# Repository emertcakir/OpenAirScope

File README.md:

EMC
------
# OpenAirScope 🌍💨

**OpenAirScope** is an open-source hardware and software project designed for advanced environmental monitoring and air quality measurement. It is based on the STM32H743 and ESP32-C3, supports LoRaWAN, and is equipped with a wide range of up-to-date sensors and display options.

### PCB 3D

## Features

* **High-Performance MCU**:

  * STM32H743 (ARM Cortex-M7, 400 MHz)
  * Capable of running advanced algorithms and real-time data processing
  * Multiple communication interfaces (I²C, SPI, UART, CAN, USB, RS485)

* **Wireless Communication**:

  * **ESP32-C3-WROOM-02** → Wi-Fi + Bluetooth LE
  * **RAK3172 (LoRaWAN)** → Low-power, long-range wireless communication
  * External **SMA antenna connector** (for LoRa)

* **Sensor Support (Optional/Modular)**:

  * **SGP41-D-R4** → Gas sensor (VOC and NOx measurement)
  * **SCD40-D-R2** → CO₂, temperature, and humidity sensor
  * **SPS30** → Particulate matter sensor (PM1.0, PM2.5, PM4, PM10)
  * **LTR-303ALS-01 (Optional)** → Ambient light sensor
  * **SPH0645LM4H-B (2 units)** → Digital MEMS microphone (ambient noise, sound level, acoustic analysis)
  * Expandable design: additional sensors such as pressure or UV can be integrated

* **Display**:

  * **1.5-inch RGB OLED Display Module**
  * 65K RGB colors, 128×128 resolution
  * SPI interface for fast graphics and real-time data visualization

* **Power Management**:

  * **Li-Ion battery support**
  * USB-powered with **simultaneous battery charging**
  * Suitable for both portable and stationary applications

* **Flexible Communication**:

  * USB-C interface
  * RS485 (for industrial environments)
  * CAN-Bus support
  * IoT integration via Wi-Fi and LoRaWAN

* **Modular Design**:

  * Optional sensor add/remove capability
  * External SMA antenna for long-range connectivity
  * Developer-friendly accessible pinout

* **Software**:

  * STM32CubeIDE / PlatformIO support
  * Open-source drivers and example libraries
  * Example algorithms for air quality and environmental data evaluation
  * OLED display example code for real-time visualization of sensor data

## Use Cases

* Smart city solutions
* Industrial environment monitoring
* Indoor/outdoor air quality tracking
* Noise pollution and sound analysis
* Portable IoT devices with OLED display
* Long-range LoRaWAN field applications
* Research and education projects

## Contributing

This project is open source. Contributions are welcome for new sensor support, software development, or documentation improvements. You can submit pull requests or open issues.

## License

Released under the MIT License.

CRITICAL WARNING: This PCB design is currently an experimental, unverified prototype (AS-IS). I have not yet manufactured or functionally tested this version. Proceeding with production carries a high risk of failure and is undertaken solely at your own risk.
---

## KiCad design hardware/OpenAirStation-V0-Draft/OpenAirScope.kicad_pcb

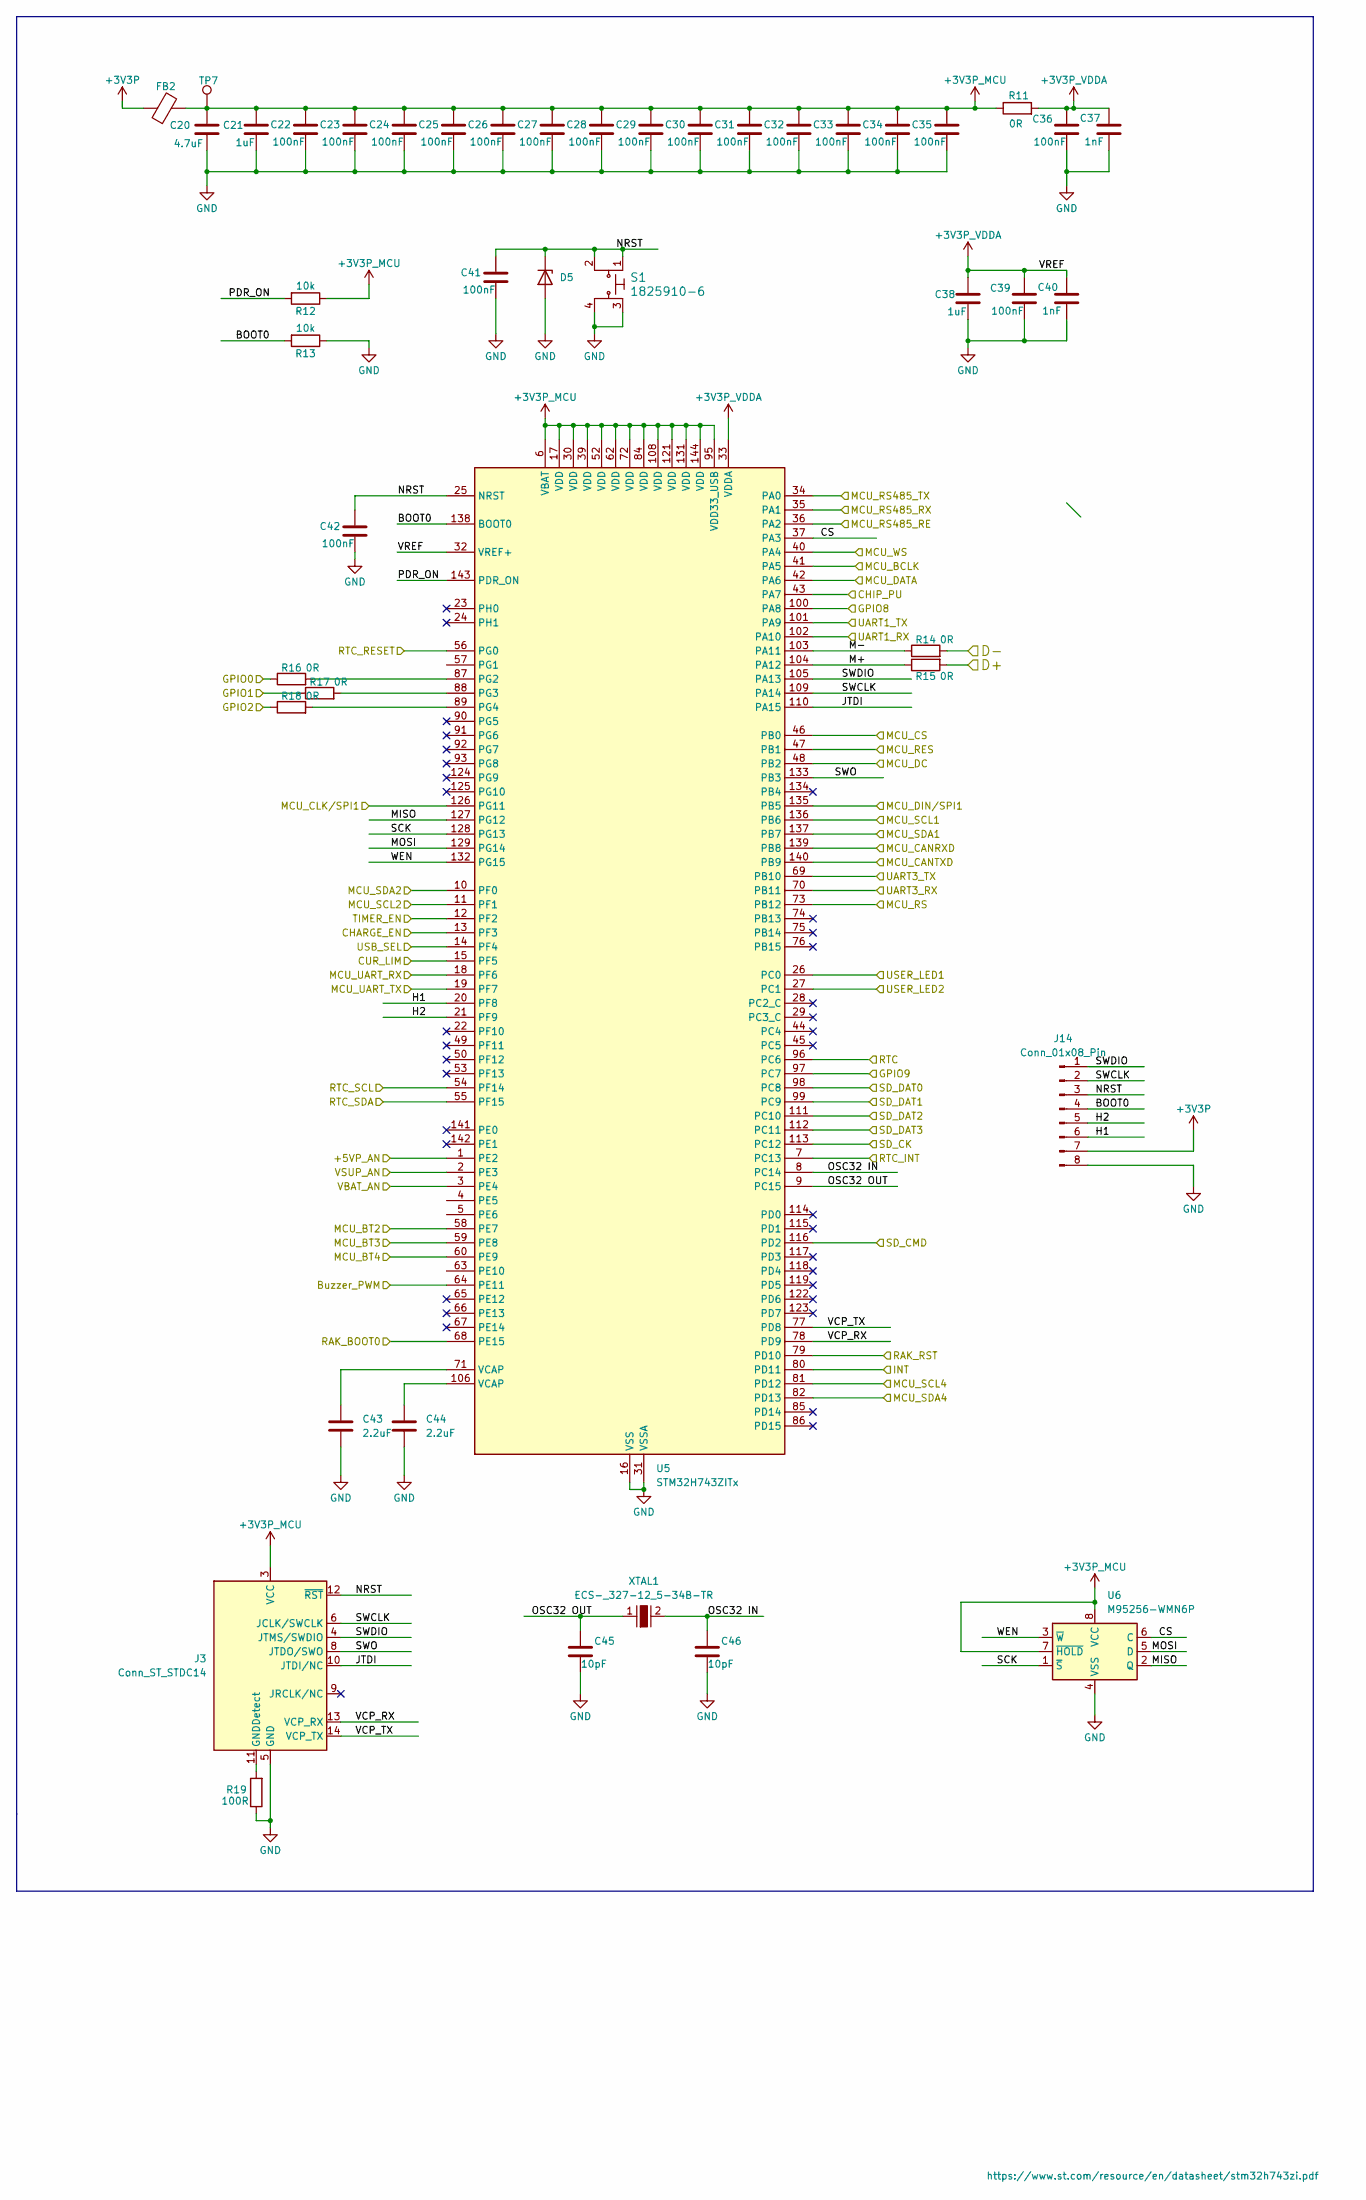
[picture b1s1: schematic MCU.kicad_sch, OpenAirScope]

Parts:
C20: 4.7uF; C_0805_2012Metric
C21, C38: 1uF; C_1206_3216Metric
C22, C23, C24, C25, C26, C27, C28, C29, C30, C31, C32, C33, C34, C35, C36, C39, C41, C42: 100nF; C_0603_1608Metric
C37, C40: 1nF; C_0603_1608Metric
C43, C44: 2.2uF; C_1206_3216Metric
C45, C46: 10pF; C_0603_1608Metric
D5: PTVS5V0Z1USKYL; Nexperia_DSN1608-2_1.6x0.8mm
FB2: FerriteBead; L_0603_1608Metric
J3: Conn_ST_STDC14; PinHeader_2x07_P1.27mm_Vertical
J14: Conn_01x08_Pin; PinHeader_1x08_P2.54mm_Vertical
R11, R14, R15, R16, R17, R18: 0R; R_0603_1608Metric
R12, R13: 10k; R_0603_1608Metric
R19: 100R; R_0603_1608Metric
S1: 1825910-6; Switch_Tactile_THT_6x6mm; MPN 1825910-6; Digi-Key_PN 450-1650-ND
TP7: TestPoint; TestPoint_Pad_D1.0mm
U5: STM32H743ZITx; LQFP-144_20x20mm_P0.5mm
U6: M95256-WMN6P; SOIC-8_3.9x4.9mm_P1.27mm
XTAL1: ECS-_327-12_5-34B-TR; SMD-2_3.2x1.5mm; MPN ECS-.327-12.5-34B-TR; Digi-Key_PN XC1617CT-ND

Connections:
+3V3P: FB2.1, J14.7; also elsewhere on the board
+3V3P_MCU: C20.1, C21.1, C22.2, C23.2, C24.2, C25.2, C26.2, C27.2, C28.2, C29.2, C30.2, C31.2, C32.2, C33.2, C34.2, C35.2, FB2.2, J3.3 (VCC), R11.1, R12.1, TP7.1, U5.6 (VBAT), U5.17 (VDD), U5.30 (VDD), U5.39 (VDD), U5.52 (VDD), U5.62 (VDD), U5.72 (VDD), U5.84 (VDD), U5.95 (VDD33_USB), U5.108 (VDD), U5.121 (VDD), U5.131 (VDD), U5.144 (VDD), U6.7 (~HOLD), U6.8 (VCC)
+3V3P_VDDA: C36.2, C37.1, C38.1, C39.2, C40.1, R11.2, U5.32 (VREF+), U5.33 (VDDA)
/Conn/A+: U5.101 (PA9); also elsewhere on the board
/Conn/A-: U5.102 (PA10); also elsewhere on the board
/Conn/CAN+: U5.139 (PB8); also elsewhere on the board
/Conn/CAN-: U5.140 (PB9); also elsewhere on the board
/Conn/CHIP_PU: U5.43 (PA7); also elsewhere on the board
/Conn/GPIO0: R16.1; also elsewhere on the board
/Conn/GPIO1: R17.1; also elsewhere on the board
/Conn/GPIO2: R18.1; also elsewhere on the board
/Conn/GPIO8: U5.100 (PA8); also elsewhere on the board
/Conn/GPIO9: U5.97 (PC7); also elsewhere on the board
/Conn/RAKRX+: U5.69 (PB10); also elsewhere on the board
/Conn/RAKTX+: U5.70 (PB11); also elsewhere on the board
/Conn/RAK_BOOT0: U5.68 (PE15); also elsewhere on the board
/Conn/RS: U5.73 (PB12); also elsewhere on the board
/Conn/RS485_RE: U5.36 (PA2); also elsewhere on the board
/Conn/RS485_RX: U5.34 (PA0); also elsewhere on the board
/Conn/RS485_TX: U5.35 (PA1); also elsewhere on the board
/Conn/RST: U5.79 (PD10); also elsewhere on the board
/Display-RTC/Buzzer_PWM: U5.64 (PE11); also elsewhere on the board
/Display-RTC/CLK: U5.126 (PG11); also elsewhere on the board
/Display-RTC/CS: U5.46 (PB0); also elsewhere on the board
/Display-RTC/DC: U5.48 (PB2); also elsewhere on the board
/Display-RTC/DIN: U5.135 (PB5); also elsewhere on the board
/Display-RTC/RES: U5.47 (PB1); also elsewhere on the board
/Display-RTC/RTC: U5.96 (PC6); also elsewhere on the board
/Display-RTC/RTC_INT: U5.7 (PC13); also elsewhere on the board
/Display-RTC/RTC_RESET: U5.56 (PG0); also elsewhere on the board
/Display-RTC/RTC_SCL: U5.54 (PF14); also elsewhere on the board
/Display-RTC/RTC_SDA: U5.55 (PF15); also elsewhere on the board
/Display-RTC/SD_CK: U5.113 (PC12); also elsewhere on the board
/Display-RTC/SD_CMD: U5.116 (PD2); also elsewhere on the board
/Display-RTC/SD_DAT0: U5.98 (PC8); also elsewhere on the board
/Display-RTC/SD_DAT1: U5.99 (PC9); also elsewhere on the board
/Display-RTC/SD_DAT2: U5.111 (PC10); also elsewhere on the board
/Display-RTC/SD_DAT3: U5.112 (PC11); also elsewhere on the board
/Indicators/+5VP_AN: U5.1 (PE2); also elsewhere on the board
/Indicators/BT2: U5.58 (PE7); also elsewhere on the board
/Indicators/BT3: U5.59 (PE8); also elsewhere on the board
/Indicators/BT4: U5.60 (PE9); also elsewhere on the board
/Indicators/USER_LED1: U5.26 (PC0); also elsewhere on the board
/Indicators/USER_LED2: U5.27 (PC1); also elsewhere on the board
/Indicators/VBAT_AN: U5.3 (PE4); also elsewhere on the board
/Indicators/VSUP_AN: U5.2 (PE3); also elsewhere on the board
/MCU/BOOT0: J14.4, R13.2, U5.138 (BOOT0)
/MCU/CHARGE_EN: U5.13 (PF3); also elsewhere on the board
/MCU/CS: U5.37 (PA3), U6.6 (C)
/MCU/CUR_LIM: U5.15 (PF5); also elsewhere on the board
/MCU/D+: R15.2; also elsewhere on the board
/MCU/D-: R14.2; also elsewhere on the board
/MCU/H1: J14.6, U5.20 (PF8)
/MCU/H2: J14.5, U5.21 (PF9)
/MCU/INT: U5.80 (PD11); also elsewhere on the board
/MCU/JTDI: J3.10 (JTDI/NC), U5.110 (PA15)
/MCU/M+: R15.1, U5.104 (PA12)
/MCU/M-: R14.1, U5.103 (PA11)
/MCU/MCU_BCLK: U5.41 (PA5); also elsewhere on the board
/MCU/MCU_DATA: U5.42 (PA6); also elsewhere on the board
/MCU/MCU_SCL1: U5.136 (PB6); also elsewhere on the board
/MCU/MCU_SCL2: U5.11 (PF1); also elsewhere on the board
/MCU/MCU_SCL4: U5.81 (PD12); also elsewhere on the board
/MCU/MCU_SDA1: U5.137 (PB7); also elsewhere on the board
/MCU/MCU_SDA2: U5.10 (PF0); also elsewhere on the board
/MCU/MCU_SDA4: U5.82 (PD13); also elsewhere on the board
/MCU/MCU_WS: U5.40 (PA4); also elsewhere on the board
/MCU/MISO: U5.127 (PG12), U6.2 (Q)
/MCU/MOSI: U5.129 (PG14), U6.5 (D)
/MCU/NRST: C41.2, C42.2, D5.1 (K), J3.12 (~RST), J14.3, S1.1, S1.2, U5.25 (NRST)
/MCU/OSC32 IN: C46.2, U5.8 (PC14), XTAL1.2
/MCU/OSC32 OUT: C45.2, U5.9 (PC15), XTAL1.1
/MCU/PDR_ON: R12.2, U5.143 (PDR_ON)
/MCU/SCK: U5.128 (PG13), U6.1 (~S)
/MCU/SWCLK: J3.6 (JCLK/SWCLK), J14.2, U5.109 (PA14)
/MCU/SWDIO: J3.4 (JTMS/SWDIO), J14.1, U5.105 (PA13)
/MCU/SWO: J3.8 (JTDO/SWO), U5.133 (PB3)
/MCU/TIMER_EN: U5.12 (PF2); also elsewhere on the board
/MCU/USB_SEL: U5.14 (PF4); also elsewhere on the board
/MCU/VCP_RX: J3.13 (VCP_RX), U5.78 (PD9)
/MCU/VCP_TX: J3.14 (VCP_TX), U5.77 (PD8)
/MCU/WEN: U5.132 (PG15), U6.3 (~W)
/Sensors/L+: U5.19 (PF7); also elsewhere on the board
/Sensors/L-: U5.18 (PF6); also elsewhere on the board
GND: C20.2, C21.2, C22.1, C23.1, C24.1, C25.1, C26.1, C27.1, C28.1, C29.1, C30.1, C31.1, C32.1, C33.1, C34.1, C35.1, C36.1, C37.2, C38.2, C39.1, C40.2, C41.1, C42.1, C43.2, C44.2, C45.1, C46.1, D5.2 (A), J3.5 (GND), J3.7 (GND), J14.8, R13.1, R19.1, S1.3, S1.4, U5.16 (VSS), U5.31 (VSSA), U5.38 (VSS), U5.51 (VSS), U5.61 (VSS), U5.83 (VSS), U5.94 (VSS), U5.107 (VSS), U5.120 (VSS), U5.130 (VSS), U6.4 (VSS); also elsewhere on the board
unnamed: C43.1, U5.71 (VCAP)
unnamed: C44.1, U5.106 (VCAP)
unnamed: J3.11 (GNDDetect), R19.2
unnamed: R16.2, U5.87 (PG2)
unnamed: R17.2, U5.88 (PG3)
unnamed: R18.2, U5.89 (PG4)

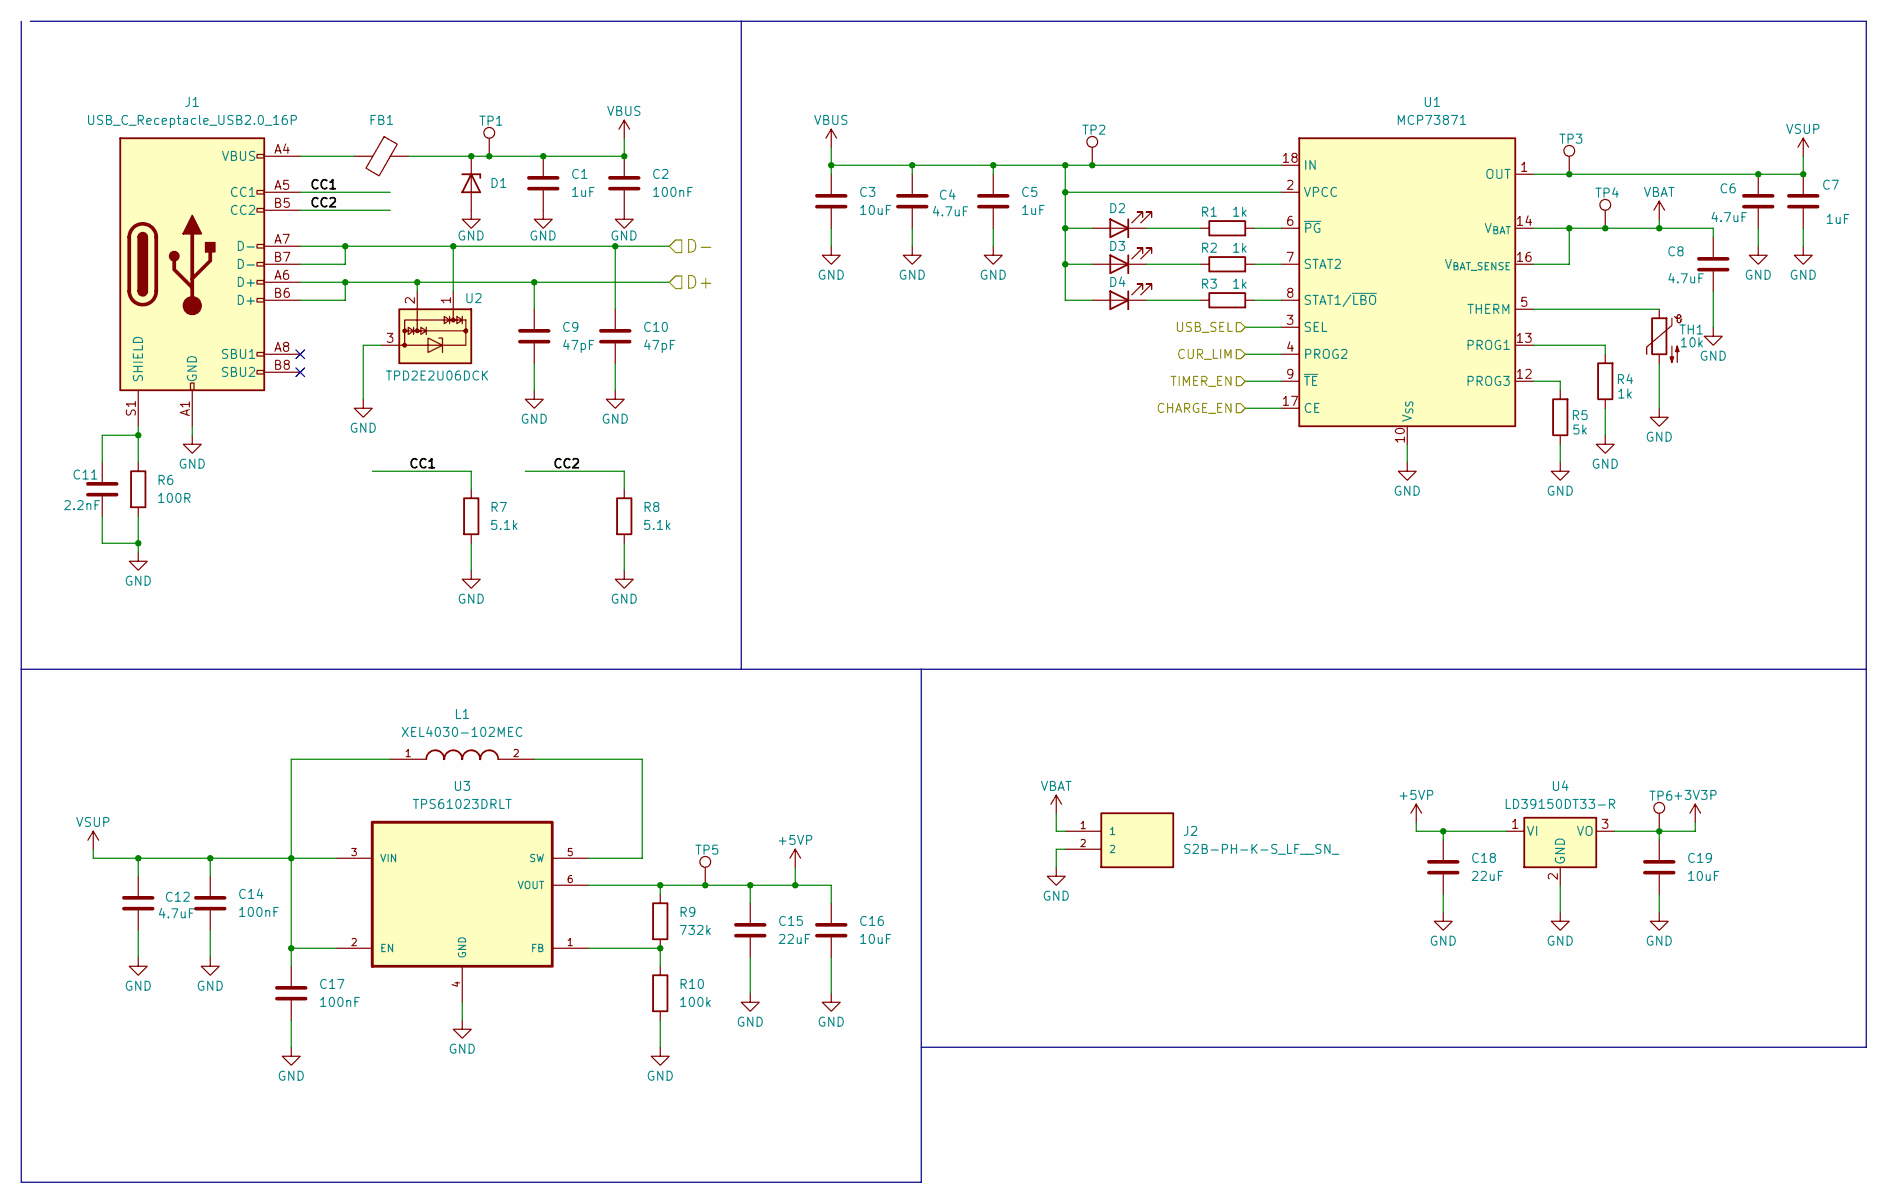
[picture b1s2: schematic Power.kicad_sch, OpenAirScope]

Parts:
C1, C5, C7: 1uF; C_1206_3216Metric
C2, C14, C17: 100nF; C_0603_1608Metric
C3, C16, C19: 10uF; C_1206_3216Metric
C4, C6, C8, C12: 4.7uF; C_0805_2012Metric
C9, C10: 47pF; C_0603_1608Metric
C11: 2.2nF; C_0805_2012Metric
C15, C18: 22uF; C_1206_3216Metric
D1: PTVS5V0Z1USKYL; Nexperia_DSN1608-2_1.6x0.8mm
D2, D3, D4: LED; LED_0603_1608Metric
FB1: FerriteBead; L_0603_1608Metric
J1: USB_C_Receptacle_USB2.0_16P; USB_C_Receptacle_GCT_USB4110
J2: S2B-PH-K-S_LF__SN_; JST_S2B-PH-K-S_LF__SN_
L1: XEL4030-102MEC; IND_XEL4030-102MEC; PARTREV 05/10/24
R1, R2, R3, R4: 1k; R_0603_1608Metric
R5: 5k; R_0603_1608Metric
R6: 100R; R_0603_1608Metric
R7, R8: 5.1k; R_0603_1608Metric
R9: 732k; R_0603_1608Metric
R10: 100k; R_0603_1608Metric
TH1: 10k; R_0603_1608Metric
TP1, TP2, TP3, TP4, TP5, TP6: TestPoint; TestPoint_Pad_D1.0mm
U1: MCP73871; QFN-20-1EP_4x4mm_P0.5mm_EP2.5x2.5mm_ThermalVias
U2: TPD2E2U06DCK; SOT-323_SC-70
U3: TPS61023DRLT; SOT50P160X60-6N
U4: LD39150DT33-R; TO-252-3_TabPin2

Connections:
+3V3P: C19.1, TP6.1, U4.3 (VO); also elsewhere on the board
+5VP: C15.1, C16.1, C18.1, R9.1, TP5.1, U3.6 (VOUT), U4.1 (VI); also elsewhere on the board
/MCU/CHARGE_EN: U1.17 (CE); also elsewhere on the board
/MCU/CUR_LIM: U1.4 (PROG2); also elsewhere on the board
/MCU/D+: C9.1, J1.A6 (D+), J1.B6 (D+), U2.2; also elsewhere on the board
/MCU/D-: C10.1, J1.A7 (D-), J1.B7 (D-), U2.1; also elsewhere on the board
/MCU/TIMER_EN: U1.9 (~TE); also elsewhere on the board
/MCU/USB_SEL: U1.3 (SEL); also elsewhere on the board
/Power/CC1: J1.A5 (CC1), R7.1
/Power/CC2: J1.B5 (CC2), R8.1
GND: C1.2, C2.2, C3.2, C4.2, C5.2, C6.2, C7.2, C8.2, C9.2, C10.2, C11.2, C12.2, C14.2, C15.2, C16.2, C17.2, C18.2, C19.2, D1.2 (A), J1.A1 (GND), J1.A12 (GND), J1.B1 (GND), J1.B12 (GND), J2.2, R4.1, R5.1, R6.2, R7.2, R8.2, R10.2, TH1.2, U1.10 (V_{SS}), U1.11 (V_{SS}), U1.21 (V_{SS}), U2.3, U3.4 (GND), U4.2 (GND); also elsewhere on the board
unnamed: D2.1 (K), R1.1
unnamed: D3.1 (K), R2.1
unnamed: D4.1 (K), R3.1
unnamed: FB1.2, J1.A4 (VBUS), J1.A9 (VBUS), J1.B4 (VBUS), J1.B9 (VBUS)
unnamed: C11.1, J1.S1 (SHIELD), R6.1
unnamed: R4.2, U1.13 (PROG1)
unnamed: R5.2, U1.12 (PROG3)
unnamed: R3.2, U1.8 (STAT1/~LBO)
unnamed: R2.2, U1.7 (STAT2)
unnamed: TH1.1, U1.5 (THERM)
unnamed: R1.2, U1.6 (~PG)
unnamed: R9.2, R10.1, U3.1 (FB)
unnamed: L1.2, U3.5 (SW)
VBAT: C8.1, J2.1, TP4.1, U1.14 (V_{BAT}), U1.15 (V_{BAT}), U1.16 (V_{BAT_SENSE}); also elsewhere on the board
VBUS: C1.1, C2.1, C3.1, C4.1, C5.1, D1.1 (K), D2.2 (A), D3.2 (A), D4.2 (A), FB1.1, TP1.1, TP2.1, U1.2 (VPCC), U1.18 (IN), U1.19 (IN)
VSUP: C6.1, C7.1, C12.1, C14.1, C17.1, L1.1, TP3.1, U1.1 (OUT), U1.20 (OUT), U3.2 (EN), U3.3 (VIN); also elsewhere on the board

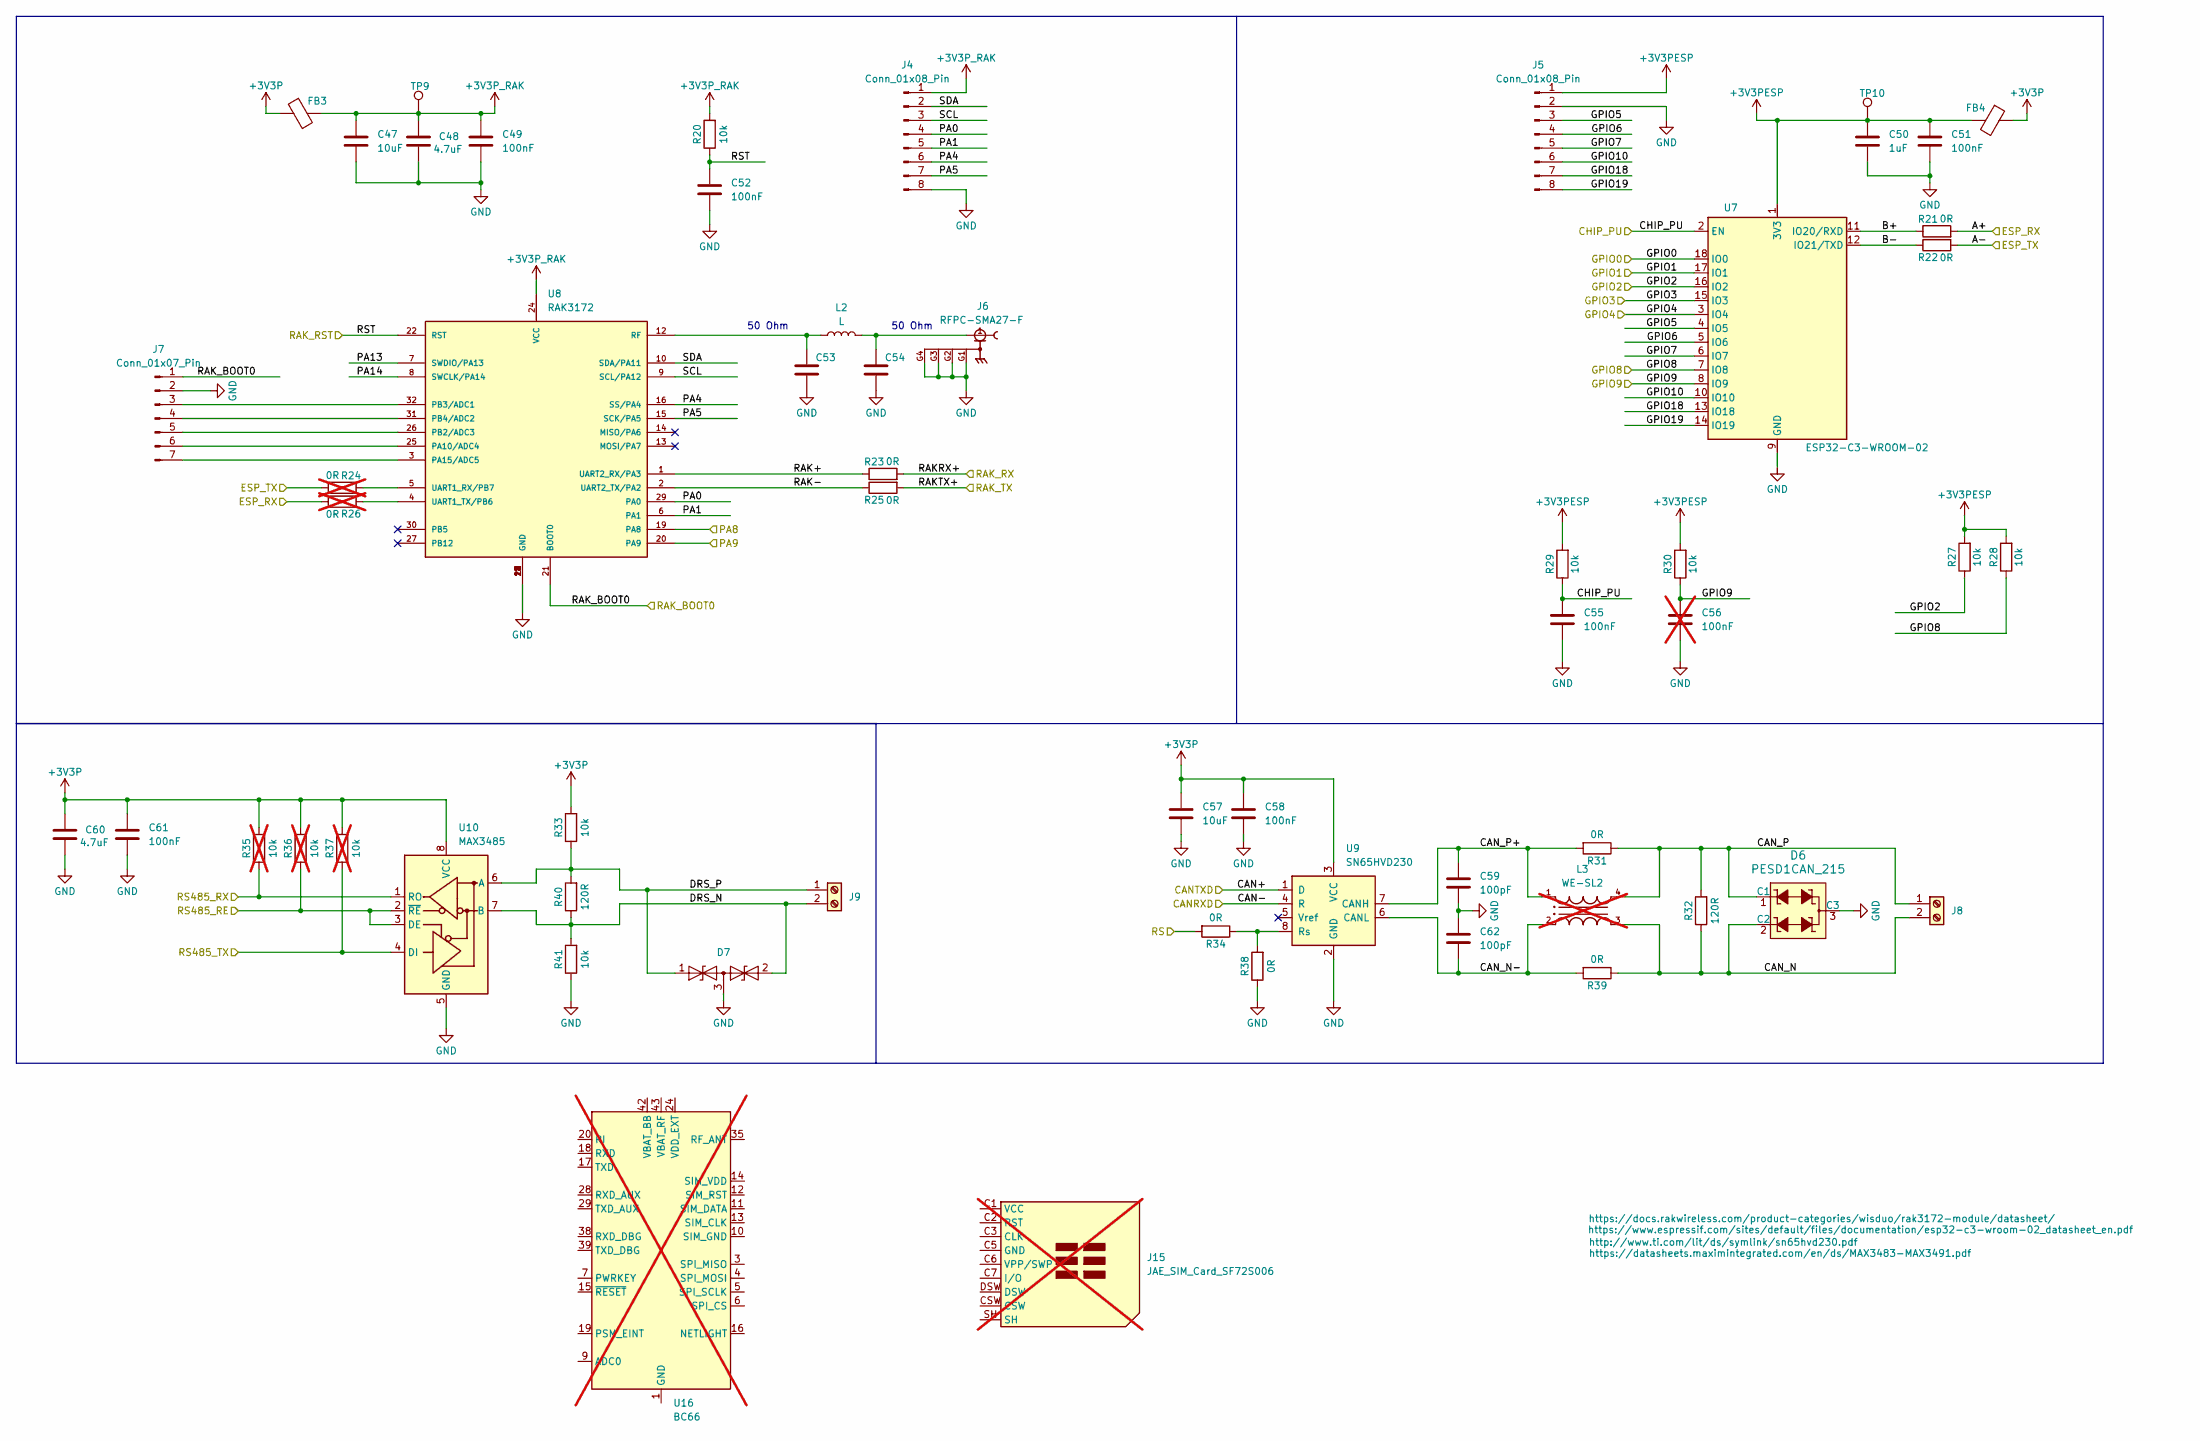
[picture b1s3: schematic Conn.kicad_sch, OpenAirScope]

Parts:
C47, C57: 10uF; C_1206_3216Metric
C48, C60: 4.7uF; C_0805_2012Metric
C49, C51, C52, C55, C58, C61: 100nF; C_0603_1608Metric
C50: 1uF; C_1206_3216Metric
C53, C54: C_0402_1005Metric
C56: 100nF; C_0603_1608Metric; not fitted
C59, C62: 100pF; C_0603_1608Metric
D6: PESD1CAN_215; SOT-23-3; MPN PESD1CAN,215; Digi-Key_PN 1727-3817-1-ND
D7: SM712_SOT23; SOT-23
FB3, FB4: FerriteBead; L_0603_1608Metric
J4, J5: Conn_01x08_Pin; PinHeader_1x08_P2.54mm_Vertical
J6: RFPC-SMA27-F; GRADCONN_RFPC-SMA27-F; PARTREV 1.0
J7: Conn_01x07_Pin; PinHeader_1x07_P2.54mm_Vertical
J8, J9: Screw_Terminal_01x02; TerminalBlock_RND_205-00045_1x02_P5.00mm_Horizontal
J15: JAE_SIM_Card_SF72S006; SD_Card_Device_16mm_SlotDepth; not fitted
L2: L; L_0603_1608Metric
L3: WE-SL2; not fitted
R20, R27, R28, R29, R30, R33, R41: 10k; R_0603_1608Metric
R21, R22, R23, R25, R31, R34, R38, R39: 0R; R_0603_1608Metric
R24, R26: 0R; R_0603_1608Metric; not fitted
R32, R40: 120R; R_0603_1608Metric
R35, R36, R37: 10k; R_0603_1608Metric; not fitted
TP9, TP10: TestPoint; TestPoint_Pad_D1.0mm
U7: ESP32-C3-WROOM-02
U8: RAK3172
U9: SN65HVD230; SOIC-8_3.9x4.9mm_P1.27mm
U10: MAX3485; SOIC-8_3.9x4.9mm_P1.27mm
U16: BC66; Quectel_BC66; not fitted

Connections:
+3V3P: C57.1, C58.1, C60.1, C61.1, FB3.1, FB4.1, R33.2, R35.2, R36.2, R37.2, U9.3 (VCC), U10.8 (VCC); also elsewhere on the board
+3V3PESP: C50.1, C51.1, FB4.2, J5.1, R27.2, R28.2, R29.2, R30.2, TP10.1, U7.1 (3V3)
+3V3P_RAK: C47.1, C48.1, C49.1, FB3.2, J4.1, R20.2, TP9.1, U8.24 (VCC)
/Conn/A+: R21.2, R26.2; also elsewhere on the board
/Conn/A-: R22.2, R24.2; also elsewhere on the board
/Conn/B+: R21.1, U7.11 (IO20/RXD)
/Conn/B-: R22.1, U7.12 (IO21/TXD)
/Conn/CAN+: U9.1 (D); also elsewhere on the board
/Conn/CAN-: U9.4 (R); also elsewhere on the board
/Conn/CAN_N: D6.2 (C2), J8.2, L3.3, R32.1, R39.1
/Conn/CAN_N-: C62.2, L3.2, R39.2, U9.6 (CANL)
/Conn/CAN_P: D6.1 (C1), J8.1, L3.4, R31.1, R32.2
/Conn/CAN_P+: C59.1, L3.1, R31.2, U9.7 (CANH)
/Conn/CHIP_PU: C55.1, R29.1, U7.2 (EN); also elsewhere on the board
/Conn/DRS_N: D7.2 (A2), J9.2, R40.1, R41.2, U10.7 (B)
/Conn/DRS_P: D7.1 (A1), J9.1, R33.1, R40.2, U10.6 (A)
/Conn/GPIO0: U7.18 (IO0); also elsewhere on the board
/Conn/GPIO1: U7.17 (IO1); also elsewhere on the board
/Conn/GPIO2: R27.1, U7.16 (IO2); also elsewhere on the board
/Conn/GPIO3: U7.15 (IO3); also elsewhere on the board
/Conn/GPIO4: U7.3 (IO4); also elsewhere on the board
/Conn/GPIO5: J5.3, U7.4 (IO5)
/Conn/GPIO6: J5.4, U7.5 (IO6)
/Conn/GPIO7: J5.5, U7.6 (IO7)
/Conn/GPIO8: R28.1, U7.7 (IO8); also elsewhere on the board
/Conn/GPIO9: C56.1, R30.1, U7.8 (IO9); also elsewhere on the board
/Conn/GPIO10: J5.6, U7.10 (IO10)
/Conn/GPIO18: J5.7, U7.13 (IO18)
/Conn/GPIO19: J5.8, U7.14 (IO19)
/Conn/PA0: J4.4, U8.29 (PA0)
/Conn/PA1: J4.5, U8.6 (PA1)
/Conn/PA4: J4.6, U8.16 (SS/PA4)
/Conn/PA5: J4.7, U8.15 (SCK/PA5)
/Conn/PA8: U8.19 (PA8); also elsewhere on the board
/Conn/PA9: U8.20 (PA9); also elsewhere on the board
/Conn/PA13: U8.7 (SWDIO/PA13)
/Conn/PA14: U8.8 (SWCLK/PA14)
/Conn/RAK+: R23.1, U8.1 (UART2_RX/PA3)
/Conn/RAK-: R25.1, U8.2 (UART2_TX/PA2)
/Conn/RAKRX+: R23.2; also elsewhere on the board
/Conn/RAKTX+: R25.2; also elsewhere on the board
/Conn/RAK_BOOT0: J7.1, U8.21 (BOOT0); also elsewhere on the board
/Conn/RS: R34.2; also elsewhere on the board
/Conn/RS485_RE: R36.1, U10.2 (~RE), U10.3 (DE); also elsewhere on the board
/Conn/RS485_RX: R35.1, U10.1 (RO); also elsewhere on the board
/Conn/RS485_TX: R37.1, U10.4 (DI); also elsewhere on the board
/Conn/RST: C52.1, R20.1, U8.22 (RST); also elsewhere on the board
/Conn/SCL: J4.3, U8.9 (SCL/PA12)
/Conn/SDA: J4.2, U8.10 (SDA/PA11)
GND: C47.2, C48.2, C49.2, C50.2, C51.2, C52.2, C53.2, C54.2, C55.2, C56.2, C57.2, C58.2, C59.2, C60.2, C61.2, C62.1, D6.3 (C3), D7.3 (common), J4.8, J5.2, J6.G1, J6.G2, J6.G3, J6.G4, J7.2, R38.1, R41.1, U7.9 (GND), U7.19 (GND), U8.11 (GND), U8.17 (GND), U8.18 (GND), U8.23 (GND), U8.28 (GND), U9.2 (GND), U10.5 (GND); also elsewhere on the board
unnamed: C54.1, J6.1, L2.2
unnamed: J7.3, U8.32 (PB3/ADC1)
unnamed: J7.4, U8.31 (PB4/ADC2)
unnamed: J7.5, U8.26 (PB2/ADC3)
unnamed: J7.6, U8.25 (PA10/ADC4)
unnamed: J7.7, U8.3 (PA15/ADC5)
unnamed: C53.1, L2.1, U8.12 (RF)
unnamed: R24.1, U8.5 (UART1_RX/PB7)
unnamed: R26.1, U8.4 (UART1_TX/PB6)
unnamed: R34.1, R38.2, U9.8 (Rs)
unnamed: U16.1 (GND), U16.27 (GND), U16.34 (GND), U16.36 (GND), U16.37 (GND), U16.40 (GND), U16.41 (GND)

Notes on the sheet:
50 Ohm

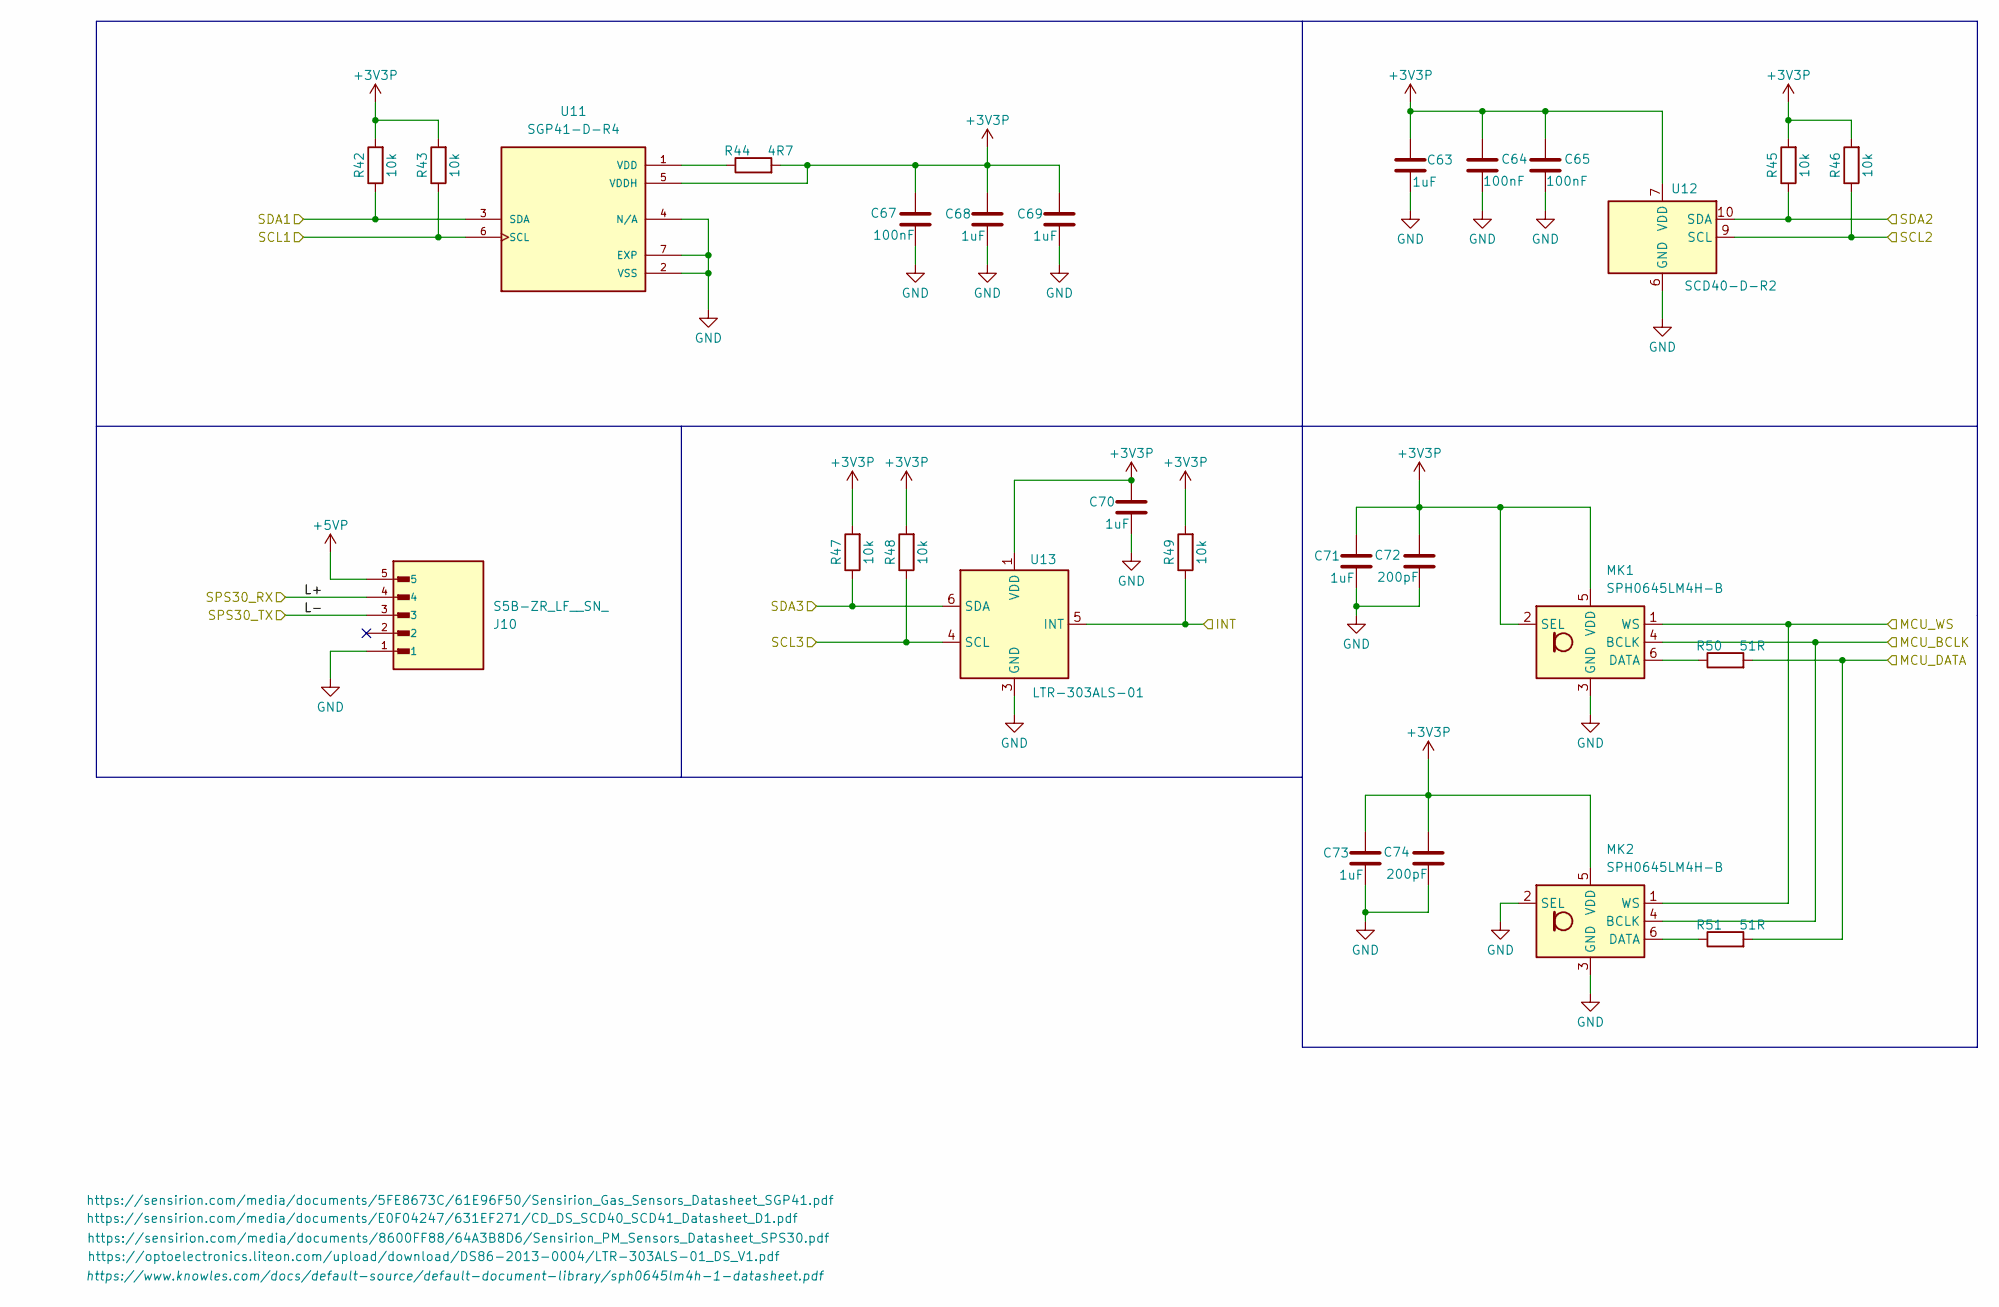
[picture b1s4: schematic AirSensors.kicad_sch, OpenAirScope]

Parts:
C63, C68, C69, C70, C71, C73: 1uF; C_1206_3216Metric
C64, C65, C67: 100nF; C_0603_1608Metric
C72, C74: 200pF; C_0603_1608Metric
J10: S5B-ZR_LF__SN_; JST_S5B-ZR_LF__SN_
MK1, MK2: SPH0645LM4H-B; Knowles_SPH0645LM4H-6_3.5x2.65mm
R42, R43, R45, R46, R47, R48, R49: 10k; R_0603_1608Metric
R44: 4R7; R_0603_1608Metric
R50, R51: 51R; R_0603_1608Metric
U11: SGP41-D-R4; XDCR_SGP41-D-R4; PARTREV 1.0
U12: SCD40-D-R2; Sensirion_SCD4x-1EP_10.1x10.1mm_P1.25mm_EP4.8x4.8mm
U13: LTR-303ALS-01; Lite-On_LTR-303ALS-01

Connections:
+3V3P: C63.1, C64.2, C65.2, C67.2, C68.1, C69.1, C70.1, C71.1, C72.2, C73.1, C74.2, MK1.2 (SEL), MK1.5 (VDD), MK2.5 (VDD), R42.2, R43.2, R44.2, R45.2, R46.2, R47.2, R48.2, R49.2, U11.5 (VDDH), U12.7 (VDD), U12.19 (VDD), U13.1 (VDD); also elsewhere on the board
+5VP: J10.5; also elsewhere on the board
/MCU/INT: R49.1, U13.5 (INT); also elsewhere on the board
/MCU/MCU_BCLK: MK1.4 (BCLK), MK2.4 (BCLK); also elsewhere on the board
/MCU/MCU_DATA: R50.2, R51.2; also elsewhere on the board
/MCU/MCU_SCL1: R42.1, U11.3 (SDA); also elsewhere on the board
/MCU/MCU_SCL2: R46.1, U12.9 (SCL); also elsewhere on the board
/MCU/MCU_SCL4: R48.1, U13.4 (SCL); also elsewhere on the board
/MCU/MCU_SDA1: R43.1, U11.6 (SCL); also elsewhere on the board
/MCU/MCU_SDA2: R45.1, U12.10 (SDA); also elsewhere on the board
/MCU/MCU_SDA4: R47.1, U13.6 (SDA); also elsewhere on the board
/MCU/MCU_WS: MK1.1 (WS), MK2.1 (WS); also elsewhere on the board
/Sensors/L+: J10.4; also elsewhere on the board
/Sensors/L-: J10.3; also elsewhere on the board
GND: C63.2, C64.1, C65.1, C67.1, C68.2, C69.2, C70.2, C71.2, C72.1, C73.2, C74.1, J10.1, MK1.3 (GND), MK2.2 (SEL), MK2.3 (GND), U11.2 (VSS), U11.4 (N/A), U11.7 (EXP), U12.6 (GND), U12.20 (GND), U12.21 (GND), U13.3 (GND); also elsewhere on the board
unnamed: MK1.6 (DATA), R50.1
unnamed: MK2.6 (DATA), R51.1
unnamed: R44.1, U11.1 (VDD)
